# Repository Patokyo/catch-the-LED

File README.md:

# catch the LED!

A tiny, USB-stick-shaped LED roulette. Nine LEDs chase around the loop and a push
button freezes the chase — whatever LED is lit when you press it is the one you
"caught".

The whole board is a USB-A plug: the tongue of the PCB *is* the connector, so it
plugs straight into any USB port for power. No cable, no adapter, no firmware.

<p align="center"><sub><b>The chase</b> — the 4017 steps one output at a time; green by the plug, then yellow, then red · shown slowed down, it really runs at ~20 Hz</sub></p>

<p align="center"><sub><b>Front</b> — nine 1210 LEDs, the 555 and 4017 as DIP-8 / DIP-16, and the USB-A PCB tongue on the left · black solder mask · LEDs drawn lit, though only one is on at a time</sub></p>

<p align="center"><sub><b>Back</b> — artwork, credits and the 4 mm mounting hole</sub></p>

## How it works

```
        ┌──────────┐   clock    ┌────────────┐   Q0…Q8    ┌──────────────┐
  USB ──┤ NE555P   ├───────────►│ CD4017     ├───────────►│ D1 … D9      │
  5 V   │ astable  │            │ decade     │            │ 1210 LEDs    │
        └──────────┘            │ counter    │            └──────┬───────┘
                                └─────┬──────┘                   │
                                      │ Q9 → Reset               │
                            SW1 ──────┴─ CKEN           R4 330Ω ──┴── GND
                       (press = freeze the chase)
```

1. **U1 (NE555P)** runs as an astable oscillator at roughly 20 Hz, set by
   R1 4k7, R2 1k and C1 10 µF.
2. **U2 (CD4017)** counts those pulses and walks one output high at a time.
   Q0…Q8 each drive one LED anode and the nine cathodes share R4 (330 Ω) to
   ground; Q9 is wired back to `Reset` so the counter rolls over after nine
   steps.
3. **SW1** pulls `CKEN` (clock enable) high, which stops the counter — the lit
   LED stays lit. R3 10k holds `CKEN` low so the chase runs by default.

## Board

| | |
|---|---|
| Size | 63.35 × 16.61 mm (2.49 × 0.65 in), USB-A plug included |
| Stack-up | 2 copper layers, 1.6 mm FR4 |
| Power | 5 V from USB-A, power only — D+ / D− are not connected |
| Current | ≈ 9 mA per lit LED (5 V − V<sub>f</sub>) / 330 Ω |
| Mounting | 4 mm hole at the far end |

## Bill of materials (catch-the-led)

| Ref | Value | Footprint |
|---|---|---|
| U1 | NE555P timer | DIP-8, 7.62 mm |
| U2 | CD4017 decade counter | DIP-16, 7.62 mm |
| D1–D9 | LEDs | 1210 / 3225 metric |
| R1 | 4k7 | 0805 |
| R2 | 1k | 0805 |
| R3 | 10k | 0805 |
| R4 | 330 | 0805 |
| C1 | 10 µF | 0805 |
| SW1 | Tactile push button, TS-1088 | SMD 4.5 × 4.5 mm |
| U3 | USB-A plug | PCB edge connector (no part to fit) |

Every placed part carries a STEP model reference from the official KiCad
library (`${KICAD9_3DMODEL_DIR}`), so the 3D viewer is complete. The USB
connector is deliberately model-less: it is bare board, not a purchased part.

## Repository layout

```
catch-the-led/                 the board (v2)
  catch-the-led.kicad_pro/-sch/-pcb
  gerbers/                     fabrication output — .gbr, .drl, .gbrjob
  gerbers/catch-the-led_gerber.zip   the same files packed for a fab house
proto-1/                       first prototype, kept for reference
  proto-1.kicad_pro/           project files (note the nested folder)
images/                        renders used in this README
```

## The prototype

`proto-1/` is kept for reference only. It had the USB pads mirrored (it only
made contact plugged in upside-down) and one LED output left unconnected;
`catch-the-led` fixes both.

## Opening and fabricating

1. Open `catch-the-led/catch-the-led.kicad_pro` in **KiCad 9**.
2. Gerbers and drills are already generated in `catch-the-led/gerbers/`; the
   packed `catch-the-led_gerber.zip` in the same folder is what to send out.
3. The USB-A tongue is bare board, so it has to be thin enough to slide into
   a port — worth mentioning to the fab when ordering.

Renders above come from KiCad's 3D raytracer (`kicad-cli pcb render`, KiCad
10) with the solder mask set to black in the board stackup.

## Credits

Designed by **Patrick Scholefield** — [github.com/Patokyo](https://github.com/Patokyo).
Silkscreen and copper artwork is hand-drawn on the boards themselves.

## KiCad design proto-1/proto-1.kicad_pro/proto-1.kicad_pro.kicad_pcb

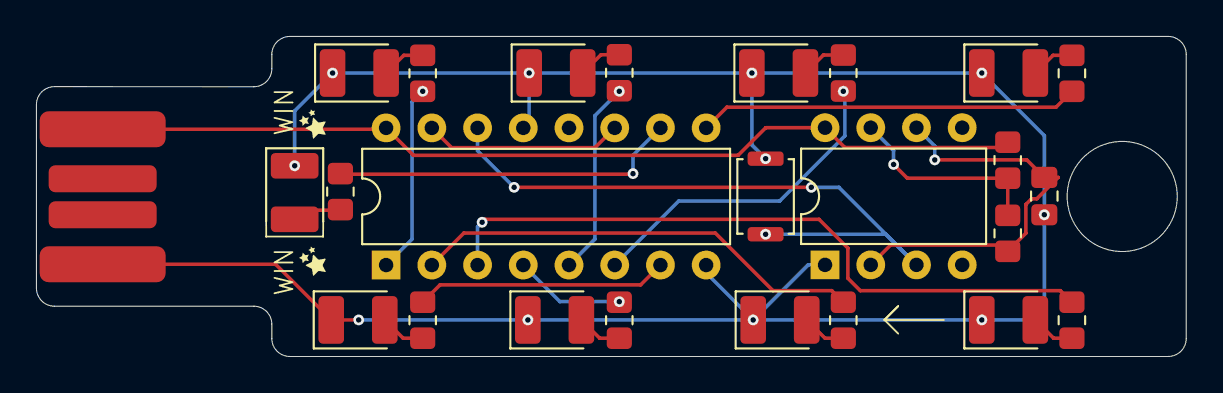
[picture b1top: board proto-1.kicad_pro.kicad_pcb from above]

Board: 2 copper layers, 63.9 x 17.8 mm, 25 parts (0 on the bottom side), 24 nets.

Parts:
C1: C; C_0805_2012Metric_Pad1.18x1.45mm_HandSolder
D1, D2, D3, D4, D5, D6, D7, D8, D9: LED; LED_1210_3225Metric_Pad1.42x2.65mm_HandSolder
R1, R2: R; R_0805_2012Metric_Pad1.20x1.40mm_HandSolder
R3, R4, R5, R6, R7, R8, R9, R10, R11: 330; R_0805_2012Metric_Pad1.20x1.40mm_HandSolder
SW1: SW_Push; SW_Push_SPST_NO_Alps_SKRK
U1: NE555P; DIP-8_W7.62mm
U2: 4017; DIP-16_W7.62mm
U3: PCB_USB_connector

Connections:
unnamed: D1.2 (A), R3.1
unnamed: C1.2, D1.1 (K), D2.1 (K), D3.1 (K), D4.1 (K), D5.1 (K), D6.1 (K), D7.1 (K), D8.1 (K), D9.1 (K), SW1.1, U1.1 (GND), U2.8 (VSS), U2.13 (CKEN), U3.4 (GND)
unnamed: D2.2 (A), R4.1
unnamed: D3.2 (A), R5.1
unnamed: D4.2 (A), R6.1
unnamed: D5.2 (A), R7.1
unnamed: D6.2 (A), R8.1
unnamed: D7.2 (A), R9.1
unnamed: D8.2 (A), R10.1
unnamed: D9.2 (A), R11.1
unnamed: R1.2, R2.1, U1.7 (DIS)
unnamed: SW1.2, U1.3 (Q), U2.14 (CLK)
unnamed: R1.1, U1.4 (R), U1.8 (VCC), U2.16 (VDD), U3.1 (VCC)
unnamed: C1.1, R2.2, U1.2 (TR), U1.6 (THR)
unnamed: R3.2, U2.3 (Q0)
unnamed: R4.2, U2.2 (Q1)
unnamed: R5.2, U2.4 (Q2)
unnamed: R6.2, U2.7 (Q3)
unnamed: R7.2, U2.10 (Q4)
unnamed: R8.2, U2.1 (Q5)
unnamed: R9.2, U2.5 (Q6)
unnamed: R10.2, U2.6 (Q7)
unnamed: R11.2, U2.9 (Q8)
unnamed: U2.11 (Q9), U2.15 (Reset)

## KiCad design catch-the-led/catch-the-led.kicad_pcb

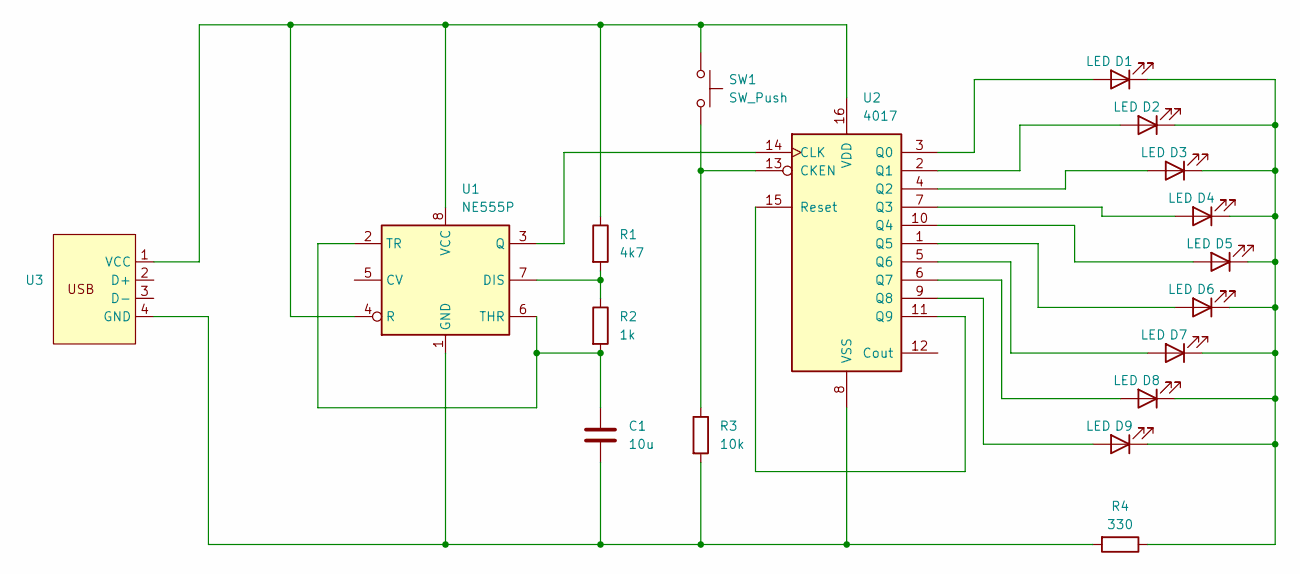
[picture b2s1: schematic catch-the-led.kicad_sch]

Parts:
C1: 10u; C_0805_2012Metric_Pad1.18x1.45mm_HandSolder
D1, D2, D3, D4, D5, D6, D7, D8, D9: LED; LED_1210_3225Metric_Pad1.42x2.65mm_HandSolder
R1: 4k7; R_0805_2012Metric_Pad1.20x1.40mm_HandSolder
R2: 1k; R_0805_2012Metric_Pad1.20x1.40mm_HandSolder
R3: 10k; R_0805_2012Metric_Pad1.20x1.40mm_HandSolder
R4: 330; R_0805_2012Metric_Pad1.20x1.40mm_HandSolder
SW1: SW_Push; SW_SPST_TS-1088-xR020
U1: NE555P; DIP-8_W7.62mm
U2: 4017; DIP-16_W7.62mm
U3: PCB_USB_connector

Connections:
unnamed: D1.2 (A), U2.3 (Q0)
unnamed: D1.1 (K), D2.1 (K), D3.1 (K), D4.1 (K), D5.1 (K), D6.1 (K), D7.1 (K), D8.1 (K), D9.1 (K), R4.1
unnamed: D2.2 (A), U2.2 (Q1)
unnamed: D3.2 (A), U2.4 (Q2)
unnamed: D4.2 (A), U2.7 (Q3)
unnamed: D5.2 (A), U2.10 (Q4)
unnamed: D6.2 (A), U2.1 (Q5)
unnamed: D7.2 (A), U2.5 (Q6)
unnamed: D8.2 (A), U2.6 (Q7)
unnamed: D9.2 (A), U2.9 (Q8)
unnamed: R1.2, R2.1, U1.7 (DIS)
unnamed: C1.2, R3.2, R4.2, U1.1 (GND), U2.8 (VSS), U3.4 (GND)
unnamed: U1.3 (Q), U2.14 (CLK)
unnamed: R1.1, SW1.1, U1.4 (R), U1.8 (VCC), U2.16 (VDD), U3.1 (VCC)
unnamed: C1.1, R2.2, U1.2 (TR), U1.6 (THR)
unnamed: R3.1, SW1.2, U2.13 (CKEN)
unnamed: U2.11 (Q9), U2.15 (Reset)

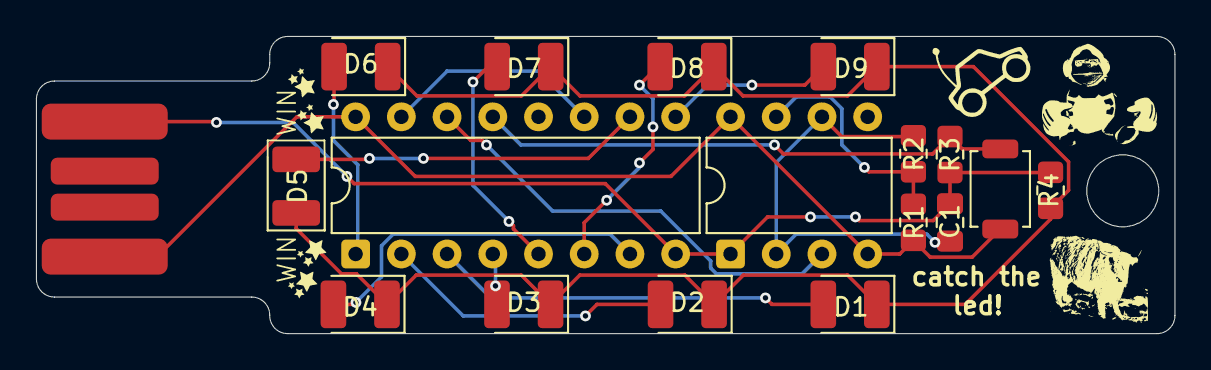
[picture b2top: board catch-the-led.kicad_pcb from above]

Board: 2 copper layers, 63.3 x 16.5 mm, 22 parts (0 on the bottom side), 17 nets.

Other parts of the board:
G: LOGO; stars
G#2, G#3, G#4: LOGO; stars

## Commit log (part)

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2025-11-06 fixed schematic
2025-11-06 finished v2
